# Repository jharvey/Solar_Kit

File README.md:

# FUGU-ARDUINO-MPPT-HARDWARE-KICAD
An open source Arduino ESP32 MPPT Solar Charge Controller firmware equipped with charging algorithms, WiFi, LCD menus &amp; more!
Stay tuned for the design release and video tutorial.<br>

Orginal Firmware project found here https://github.com/AngeloCasi/FUGU-ARDUINO-MPPT-FIRMWARE<br>
Oringal Hardware project found here https://drive.google.com/drive/folders/1Sd2jWAb-F8NAXlJ6PLdhcnPDQV0alD15?usp=sharing<br>
Oringal Hardware project found here https://github.com/haliltepedelen/EG8010-Control-Board-for-Low-Frequency-Inverter-Power-Board-12-24-48-V--5kW<br>

<div align="center">

<div align="left">
OnShape 3D found here https://cad.onshape.com/documents/5882843f0ee96e62ba8b9faf/w/820f02cb3842ce32ae850702/e/1fe43df2095ddf6be5cc563b?renderMode=0&uiState=630a19a00173156e6a7194ef<br>
GPL open-source DIY Charge Controller<br>

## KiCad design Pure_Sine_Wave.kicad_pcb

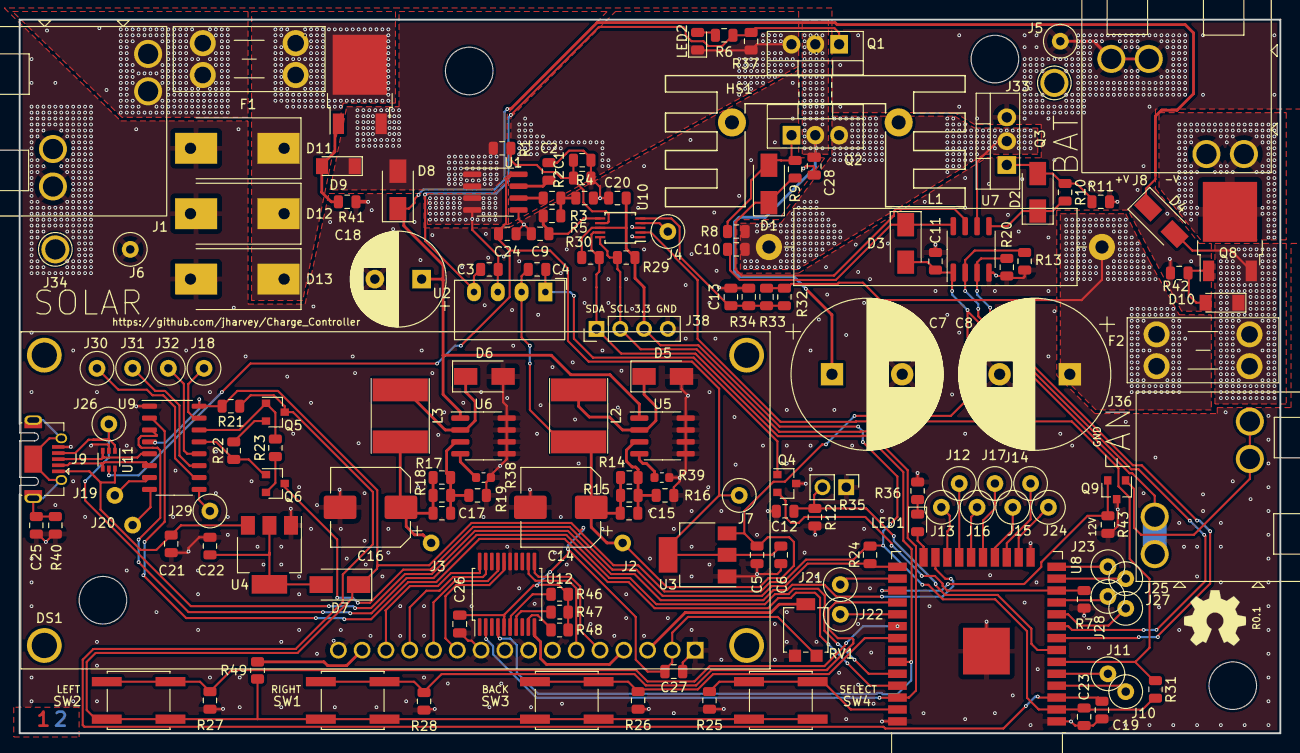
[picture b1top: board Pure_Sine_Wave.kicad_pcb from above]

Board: 2 copper layers, 134.6 x 76.2 mm, 160 parts (0 on the bottom side), 101 nets.

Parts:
C1, C3, C4, C11, C12, C13, C20, C23, C25, C26, C27, C28: 100nf; C_0805_2012Metric
C2, C9: 2.2uf; C_0805_2012Metric
C5, C6, C21, C22, C24: 4.7uf; C_0805_2012Metric
C7, C8: 470uf; CP_Radial_D16.0mm_P7.50mm
C10: 10uf; C_0805_2012Metric
C14, C16: 100uf; CP_Elec_8x10
C15, C17: 33nf; C_0805_2012Metric
C18: 4.7uf; CP_Radial_D10.0mm_P5.00mm
C19: 470nf; C_0805_2012Metric
D1, D2, D3, D5, D6, D7: SS310; D_SMA
D4, D8: 1N4007; D_SMA
D9, D10: D_Zener_Small; D_MiniMELF
D11: 90V-34A; D_SMC-RM10_Universal_Handsoldering
D12, D13: 120V-26A; D_SMC-RM10_Universal_Handsoldering
DS1: LCD; LCD_LCM-S01602DTR_A
F1, F2: 35A; Fuseholder_Blade_Mini_Keystone_3568
HS1: Heatsink; Heatsink_Stonecold_HS-132_32x14mm_2xFixation1.5mm
J1: SOLAR; Phoenix_10.16_terminal_1709681
J2, J3, J4, J5, J6, J7, J10, J11, J12, J13, J14, J15, J16, J17, J18, J19, J20, J21, J22, J23, J24, J25, J26, J27, J28, J29, J30, J31, J32, J33, J34: Conn_01x01_Female; TestPoint_Loop_D3.50mm_Drill0.9mm_Beaded
J8: BATT; Phoenix_10.16_terminal_1709681
J9: USB_OTG; USB_Micro-AB_Molex_47590-0001
J36: FAN; Phoenix_10.16_terminal_1709681
J38: I2C_CON; PinHeader_1x04_P2.54mm_Vertical
L1: 64uH; L_Axial_L30.0mm_D8.0mm_P35.56mm_Horizontal_Fastron_77A
L2, L3: 100uH; L_Taiyo-Yuden_NR-60xx_HandSoldering
LED1, LED2: LED; LED_0805_2012Metric
LOGO1: Logo_Open_Hardware_Small; OSHW-Symbol_6.7x6mm_SilkScreen
Q1, Q2, Q3: CSD19505; TO-220-3_Vertical
Q4, Q9: Si2306; SOT-23
Q5, Q6: 2N3904; SOT-23
Q7, Q8: PMOS-100V-78A; TO-252-2
R1: 200k; R_0805_2012Metric
R2: 5.1k; R_0805_2012Metric
R3: 3.3k; R_0805_2012Metric
R4, R6, R7, R12, R13, R20, R21, R22, R23, R24, R25, R26, R27, R28, R29, R30, R31, R36, R37, R43, R46, R47, R48: 10k; R_0805_2012Metric
R5, R16, R19, R34, R41, R42: 1k; R_0805_2012Metric
R8, R11, R40: 100k; R_0805_2012Metric
R9, R10: 100; R_0805_2012Metric
R14, R15, R17, R18: 15k; R_0805_2012Metric
R32, R33: 47k; R_0805_2012Metric
R35: 10k_-tc; PinHeader_1x02_P2.54mm_Vertical
R38, R39: 0R; R_0603_1608Metric
R49: 330; R_0805_2012Metric
RV1: 10k; Potentiometer_Bourns_3314G_Vertical
SW1: RIGHT; SW_SPST_EVQQ2
SW2: LEFT; SW_SPST_EVQQ2
SW3: BACK; SW_SPST_EVQQ2
SW4: SELECT; SW_SPST_EVQQ2
U1: Hall Amp Sense; SOIC-8_3.9x4.9mm_P1.27mm
U2: B1212; Converter_DCDC_muRata_CRE1xxxxxxSC_THT
U3: AMS1117-5.0; SOT-223-3_TabPin2
U4: AMS1117-3.3; SOT-223-3_TabPin2
U5, U6: XL7005A; SOIC-8_3.9x4.9mm_P1.27mm
U7: IR2104; SOIC-8_3.9x4.9mm_P1.27mm
U8: ESP32-WROOM-32
U9: CH340C; STC_SOP-16_3.9x9.9mm_P1.27mm
U10: ADS1015; TSSOP-10_3x3mm_P0.5mm
U11: NUP4202; SOT-363_SC-70-6
U12: PCF8574; SSOP-20_5.3x7.2mm_P0.65mm

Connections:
+3.3VA: C20.2, C23.2, C26.2, C27.2, D7.1 (K), DS1.2 (VDD), J38.3, R21.2, R24.2, R29.1, R30.1, R31.2, R46.1, R47.1, R48.1, R49.1, RV1.3, SW1.2, SW2.2, SW3.2, SW4.2, U8.2 (VDD), U9.4 (V3), U9.16 (VCC), U10.8 (VDD), U12.5 (VDD)
/3.3V: C16.1, C17.1, J3.1, L3.2, R17.1, R18.1
/5.0V: C6.1, C24.2, J7.1, U1.8 (VCC), U3.2 (VO), U11.5
/12V: C4.1, C5.1, C11.2, C14.1, C15.1, D3.2 (A), J2.1, J36.1, L2.2, R14.1, R15.1, U2.2 (+VIN), U3.3 (VI), U7.1 (VCC)
/A0: J4.1, U10.4 (AIN0)
/A1: C13.1, R32.2, R33.2, R34.1, U10.5 (AIN1)
/A2: C9.1, R5.1, U10.6 (AIN2)
/A3: C1.1, R1.2, R2.1, U10.7 (AIN3)
/B+: J8.1, Q8.2 (D)
/B+Fused: C8.1, F2.2, L1.2, R32.1, R33.1
/B+Polarity: D4.2 (A), D10.1 (K), F2.1, Q8.3 (S)
/BuckFB: C10.2, L1.1, Q2.3 (S), Q3.2 (D), R8.2, U7.6 (VS)
/E: DS1.6 (E), U12.12 (P2)
/EN: C19.1, Q5.3 (C), R21.1, U8.3 (EN)
/FAN-CR: Q9.2 (G), R43.1, U8.27 (IO16)
/GPIO0: Q6.3 (C), R24.1, U8.25 (IO0)
/GPIO27: Q4.2 (G), R7.1, U8.12 (IO27)
/GPIO32: R20.2, U7.3 (~SD), U8.8 (IO32)
/GPIO33: R13.2, U7.2 (IN), U8.9 (IO33)
/GPIO34: R31.1, U8.6 (IO34), U10.2 (ALERT/RDY)
/LED1: LED1.2 (A), U8.24 (IO2)
/PB-RHT: R28.2, SW1.1, U8.28 (IO17)
/PB-SEL: R25.2, SW4.1, U8.37 (IO23)
/PB_BCK: R26.2, SW3.1, U8.31 (IO19)
/PB_LFT: R27.2, SW2.1, U8.30 (IO18)
/RS: DS1.4 (RS), U12.10 (P0)
/RW: DS1.5 (R/~W), U12.11 (P1)
/RX: U8.34 (RXD0/IO3), U9.3 (RXD)
/S+: F1.1, J1.1
/S+B+1A: C18.1, D4.1 (K), D8.1 (K), U5.1 (VIN), U6.1 (VIN)
/S+Fused: D11.1 (A1), D12.1 (A1), D13.1 (A1), F1.2, Q7.2 (D)
/S+Fused2: C3.2, LED2.1 (K), Q1.3 (S), R37.1, U1.3 (IP-), U1.4 (IP-), U2.3 (-VOUT)
/S+Fused3: C7.1, C28.2, Q1.2 (D), Q2.2 (D)
/S+Polarity: D8.2 (A), D9.1 (K), Q7.3 (S), R1.1, U1.1 (IP+), U1.2 (IP+)
/SCL: J38.2, R29.2, U8.36 (IO22), U10.10 (SCL), U12.2 (SCL)
/SDA: J38.1, R30.2, U8.33 (IO21), U10.9 (SDA), U12.4 (SDA)
/TX: U8.35 (TXD0/IO1), U9.2 (TXD)
/USBID: J9.4 (ID), J26.1, U8.23 (IO15), U11.1
/USBV: C21.1, J9.1 (VBUS), U4.3 (VI), U11.6
GND: C1.2, C2.1, C5.2, C6.2, C7.2, C8.2, C9.2, C11.1, C12.1, C13.2, C14.2, C16.2, C18.2, C19.2, C20.1, C21.2, C22.2, C23.1, C24.1, C25.2, C26.1, C27.1, C28.1, D5.2 (A), D6.2 (A), D11.2 (A2), D12.2 (A2), D13.2 (A2), DS1.1 (VSS), DS1.7 (DB0), DS1.8 (DB1), DS1.9 (DB2), DS1.10 (DB3), DS1.16 (K), J1.2, J5.1, J6.1, J8.2, J9.5 (GND), J33.1, J34.1, J38.4, Q3.3 (S), Q4.3 (S), Q9.3 (S), R2.2, R4.2, R7.2, R11.2, R12.1, R13.1, R16.1, R19.1, R20.1, R25.1, R26.1, R27.1, R28.1, R34.2, R35.1, R36.1, R38.1, R39.1, R40.2, R41.2, R42.2, R43.2, RV1.1, U1.5 (GND), U3.1 (GND), U4.1 (GND), U5.5 (GND), U5.6 (GND), U5.7 (GND), U5.8 (GND), U6.5 (GND), U6.6 (GND), U6.7 (GND), U6.8 (GND), U7.4 (COM), U8.1 (GND), U8.15 (GND), U8.38 (GND), U8.39 (GND), U9.1 (GND), U10.1 (ADDR), U10.3 (GND), U11.2, U12.15 (VSS)
unnamed: C2.2, U1.7 (VIOUT)
unnamed: C3.1, Q1.1 (G), R6.2, R37.2, U2.4 (+VOUT)
unnamed: C4.2, Q4.1 (D), U2.1 (-VIN)
unnamed: C10.1, D3.1 (K), U7.8 (VB)
unnamed: C12.2, R12.2, R35.2, U8.7 (IO35)
unnamed: C15.2, R14.2, R15.2, R16.2, U5.3 (FB)
unnamed: C17.2, R17.2, R18.2, R19.2, U6.3 (FB)
unnamed: C22.1, D7.2 (A), U4.2 (VO)
unnamed: C25.1, J9.6 (Shield), R40.1
unnamed: D1.1 (K), R9.1, U7.7 (HO)
unnamed: D1.2 (A), Q2.1 (G), R8.1, R9.2
unnamed: D2.1 (K), R10.1, U7.5 (LO)
unnamed: D2.2 (A), Q3.1 (G), R10.2, R11.1
unnamed: D5.1 (K), L2.1, U5.2 (VOUT)
unnamed: D6.1 (K), L3.1, U6.2 (VOUT)
unnamed: D9.2 (A), Q7.1 (G), R41.1
unnamed: D10.2 (A), Q8.1 (G), R42.1
unnamed: DS1.3 (VO), RV1.2
unnamed: DS1.11 (DB4), U12.16 (P4)
unnamed: DS1.12 (DB5), U12.17 (P5)
unnamed: DS1.13 (DB6), U12.19 (P6)
unnamed: DS1.14 (DB7), U12.20 (P7)
unnamed: DS1.15 (A), R49.2
unnamed: J9.2 (D-), U9.6 (UD-), U11.4
unnamed: J9.3 (D+), U9.5 (UD+), U11.3
unnamed: J10.1, U8.4 (SENSOR_VP)
unnamed: J11.1, U8.5 (SENSOR_VN)
unnamed: J12.1, U8.21 (SDO/SD0)
unnamed: J13.1, U8.22 (SDI/SD1)
unnamed: J14.1, U8.17 (SHD/SD2)
unnamed: J15.1, U8.18 (SWP/SD3)
unnamed: J16.1, U8.20 (SCK/CLK)
unnamed: J17.1, U8.19 (SCS/CMD)
unnamed: J18.1, U9.15 (R232)
unnamed: J19.1, U9.7 (XI)
unnamed: J20.1, U9.8 (XO)
unnamed: J21.1, U8.26 (IO4)
unnamed: J22.1, U8.29 (IO5)
unnamed: J23.1, U8.14 (IO12)
unnamed: J24.1, U8.16 (IO13)
unnamed: J25.1, U8.13 (IO14)
unnamed: J27.1, U8.10 (IO25)
unnamed: J28.1, U8.11 (IO26)
unnamed: J29.1, U9.9 (~CTS)
unnamed: J30.1, U9.10 (~DSR)
unnamed: J31.1, U9.11 (~RI)
unnamed: J32.1, U9.12 (~DCD)
unnamed: J36.2, Q9.1 (D)
unnamed: LED1.1 (K), R36.2
unnamed: LED2.2 (A), R6.1
unnamed: Q5.1 (E), R23.2, U9.14 (~RTS)
unnamed: Q5.2 (B), R22.2
unnamed: Q6.1 (E), R22.1, U9.13 (~DTR)
unnamed: Q6.2 (B), R23.1
unnamed: R3.1, U1.6 (FILTER)
unnamed: R3.2, R4.1, R5.2
unnamed: R38.2, U6.4 (~ON/OFF)
unnamed: R39.2, U5.4 (~ON/OFF)
unnamed: R46.2, U12.6 (A0)
unnamed: R47.2, U12.7 (A1)
unnamed: R48.2, U12.9 (A2)

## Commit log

2022-09-03 Initial check in, Schematic mostly there, missing IFB 0.5V logic, Layout does not currently include the pure sine wave generator.
2022-09-04 Added Simulation for EG8010 IFB signal.
2022-09-04 Added a link to a reference for full wave rectification circuit.
2022-09-06 Updated schematic to match changes form charge controller Added simulation for MOSFET heat predictions.
2022-09-07 Created simulation drafting the heat for the Q1, Q2 MOSFETs
2022-10-05 Draft DC to DC simulation. 400Vout into 10k ohm load. Needs tuning to handle much lower load.
2022-10-13 Draft, it claims 90W at 300V and 0.3A output. However it appears to have problems, like a 1kV mid voltage.
2022-10-13 240Vout_59W drafted, still needs tuning. Vtrans still 1kv, not enough voltage not enough watts.
